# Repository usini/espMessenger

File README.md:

An 8x8 Matrix WiFi Display
--------------------------

# Features
* Responsive Web Interface
* Simple Web Request to send Message (ex: http://espmessenger/message/hello send hello)
* Accentuated characters supports
* Localization Support (French / English as for now)
* WiFiManager configuration (Nb of devices / Password and Username)
* Basic HTTP Authentication
* Discoverable using Netbios / Bonjour / SSDP
* Web Update

# Libraries used
* MD_MAX72xx
* MD_Parola
* ArduinoJSON (v6)
* WiFiManager

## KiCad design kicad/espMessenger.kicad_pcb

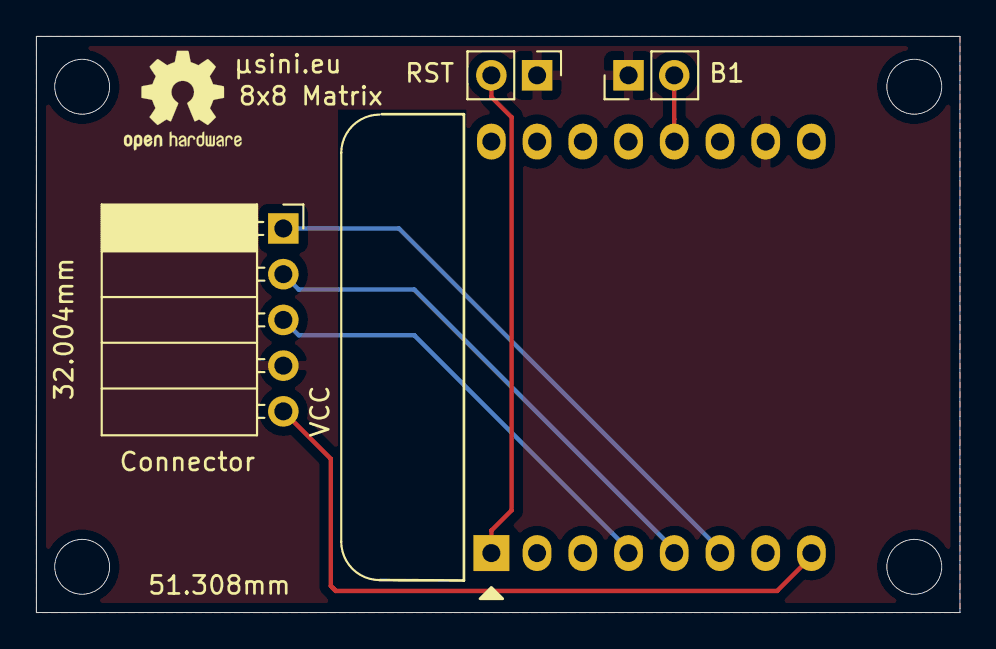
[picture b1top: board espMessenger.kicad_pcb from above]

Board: 2 copper layers, 51.3 x 32.0 mm, 4 parts (0 on the bottom side), 7 nets.

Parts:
Connector: Matrix Connector; PinSocket_1x05_P2.54mm_Horizontal
J1: RST Button; PinHeader_1x02_P2.54mm_Vertical
J3: USER Button; PinHeader_1x02_P2.54mm_Vertical
U1: WeMos_D1_mini; WEMOS_D1_mini_light_no_female_connectors

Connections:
+3V3: Connector.5, U1.8
GND: Connector.4, J1.1, J3.1, U1.10
unnamed: J1.2, U1.1
unnamed: Connector.1, U1.6
unnamed: Connector.2, U1.5
unnamed: Connector.3, U1.4
unnamed: J3.2, U1.12

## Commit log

2019-05-09 Settings / basic web
    --> Settings init
    --> Settings read to variables
    --> First web interface
2019-05-09 Settings page
    -- Settings page
    -- Save settings
    -- Reboot available (don't really works)
    -- No wait for Wifi Connection --> Crash because connecting simultanously to AP/Wifi
    -- U8glib added (not working correctly)
2019-05-10 Refactoring web/wifi - Change U8glib to MD_MAX27xx
    Copy web functions into web.h
    Copy web contents into web/
    Copy wifi functions into wifi.h
    Change U8glib to MD_MAX27
2019-05-11 Refactoring Matrix
    Added SSDP/NETBIOS / LLMNR naming convention.
2019-05-12 Replace MD_MAX72XX with MD_Parolo (UTF-8 support)
    Minor tweak to Serial logging.
2019-05-12 Add Comments
2019-05-12 Buffer overflow issue solved
    Remove unused debug in serial
2019-05-14 Testing MQTT
    Long message dropped connection
    Can't change MQTT server address
    TODO: Switch to pubsubclient
2019-05-15 Change Adafruit MQTT to pubsubclient / String management
2019-05-17 Web design in progress / add python emulator
2019-05-17 Push web design
2019-05-23 Web Design Improvement / Web SSL begin.
    Fonts move to fonts/
    Web - Disconnection detection
    Toast / Loading screen
2019-05-25 Update Web Design (Settings) / Trying SSL (non working/slow)
    --> Display IP instead of IP UNSET when in AP mode
    --> Settings time in Wifi.h (for SSL but can be used to display time)
2019-05-31 HTML --> Compressed char[] script
    Put SSDP in web.h since it is required
2019-06-04 Add auth / Improve minify.py / seperated css/js
    Authentification cause a buffer overflow in SSL
    SSL is a bit too much for this board I think
    I'll keep the code for the esp32 port
2019-06-07 Add update field / Add comments / Move part of settings into settings_value
    --> Manage checkbox.
    Have some buffer overflow :-( code has some serious issues to inspect.
    May use an ESP32 instead.
2019-11-01 Complete rework
    --> Add WifiManager
    --> Change POST json request with REST request (/message/{message})
    --> Mandatory Basic Auth
    --> Possibility to setup nb of matrices
    --> Add FR/EN language choice
2020-01-29 Add schematics / pcb and Readme
2020-02-14 Add Speed/Intensity, some bugs fixes
    --> Need to add this changes to the english version, probably improve translation to avoid this issue.
    --> Add API to change Scroll effects and alignement and pause but didn't saved it as it is a bit not really useable for a simple scrolling text.
2020-02-15 WebAuth issue / fixed translation.
2020-02-15 Added node-red flow
2020-02-15 Add alt pins in code
2020-02-16 No scrolling if no necessary / bug translation fixes
    --> Translation is made using javascript to simplify code changes
    --> Version is display on serial/web (not automatic on web for now)
    --> Scrolling is disable if text can be display entirely
    --> Fix web bugs.
